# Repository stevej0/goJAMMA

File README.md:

# goJAMMA
Game on JAMMA development board PROTOTYPE v0.2 (C) 2019 Steve Jones / BONEYARD

This is a prototype FPGA based JAMMA board for the development of homebrew games for arcade machine platforms and superguns.

The design is currently in a prototype stage, pretty much everything has been tested as working, however bugs and performance issues may remain. This design is NOT approved for production as of yet, but the files are made public as an aid to others developing their own hardware.
  
FAQ to follow...

Hardware specifications (fixed):

Altera MAX10 10M25SAE FPGA, 25K logic elements, extended Flash features  
1MB 8Bit Static RAM, 10ns access  
16MB 8Bit HyperRAM, 166Mhz DDR, 128 byte burst  
48Mhz Crystal clock oscillator  
microSD card interface  
ADC 4 channel, 10 bit analog to digital convertor (Analog inputs via expansion connector)  
Buffered video output  
Stereo audio amplifier, 11 Watts  
PCM5101 Stereo 12S DAC  
4 Way Dip Switch  
Standard JAMMA 5v tolerant inputs, plus configuration jumpers for 6-button Pandoras Box style interface  
1x USER button, 1x RESET button  
1x USER LED  
Large long-life and user replacable through hole capacitors in the audio and voltage regulator sections  

Homebrew logic core (basic wishlist) specifications, likely to change:
  
CPU core (undecided, but a 6502 at 4Mhz currently works well)  
256 Colour palette, 320 x 240 pixel framebuffer (double buffered)  
Sprites (undecided, most likely a blitter for the framebuffer with fast HyperRAM as gfx data source)  
Layers (undecided, at least one text overlay, maybe a tiled background layer also)  
16 channel sample playback  
Ability to load programs and data from microSD fat32 formatted cards

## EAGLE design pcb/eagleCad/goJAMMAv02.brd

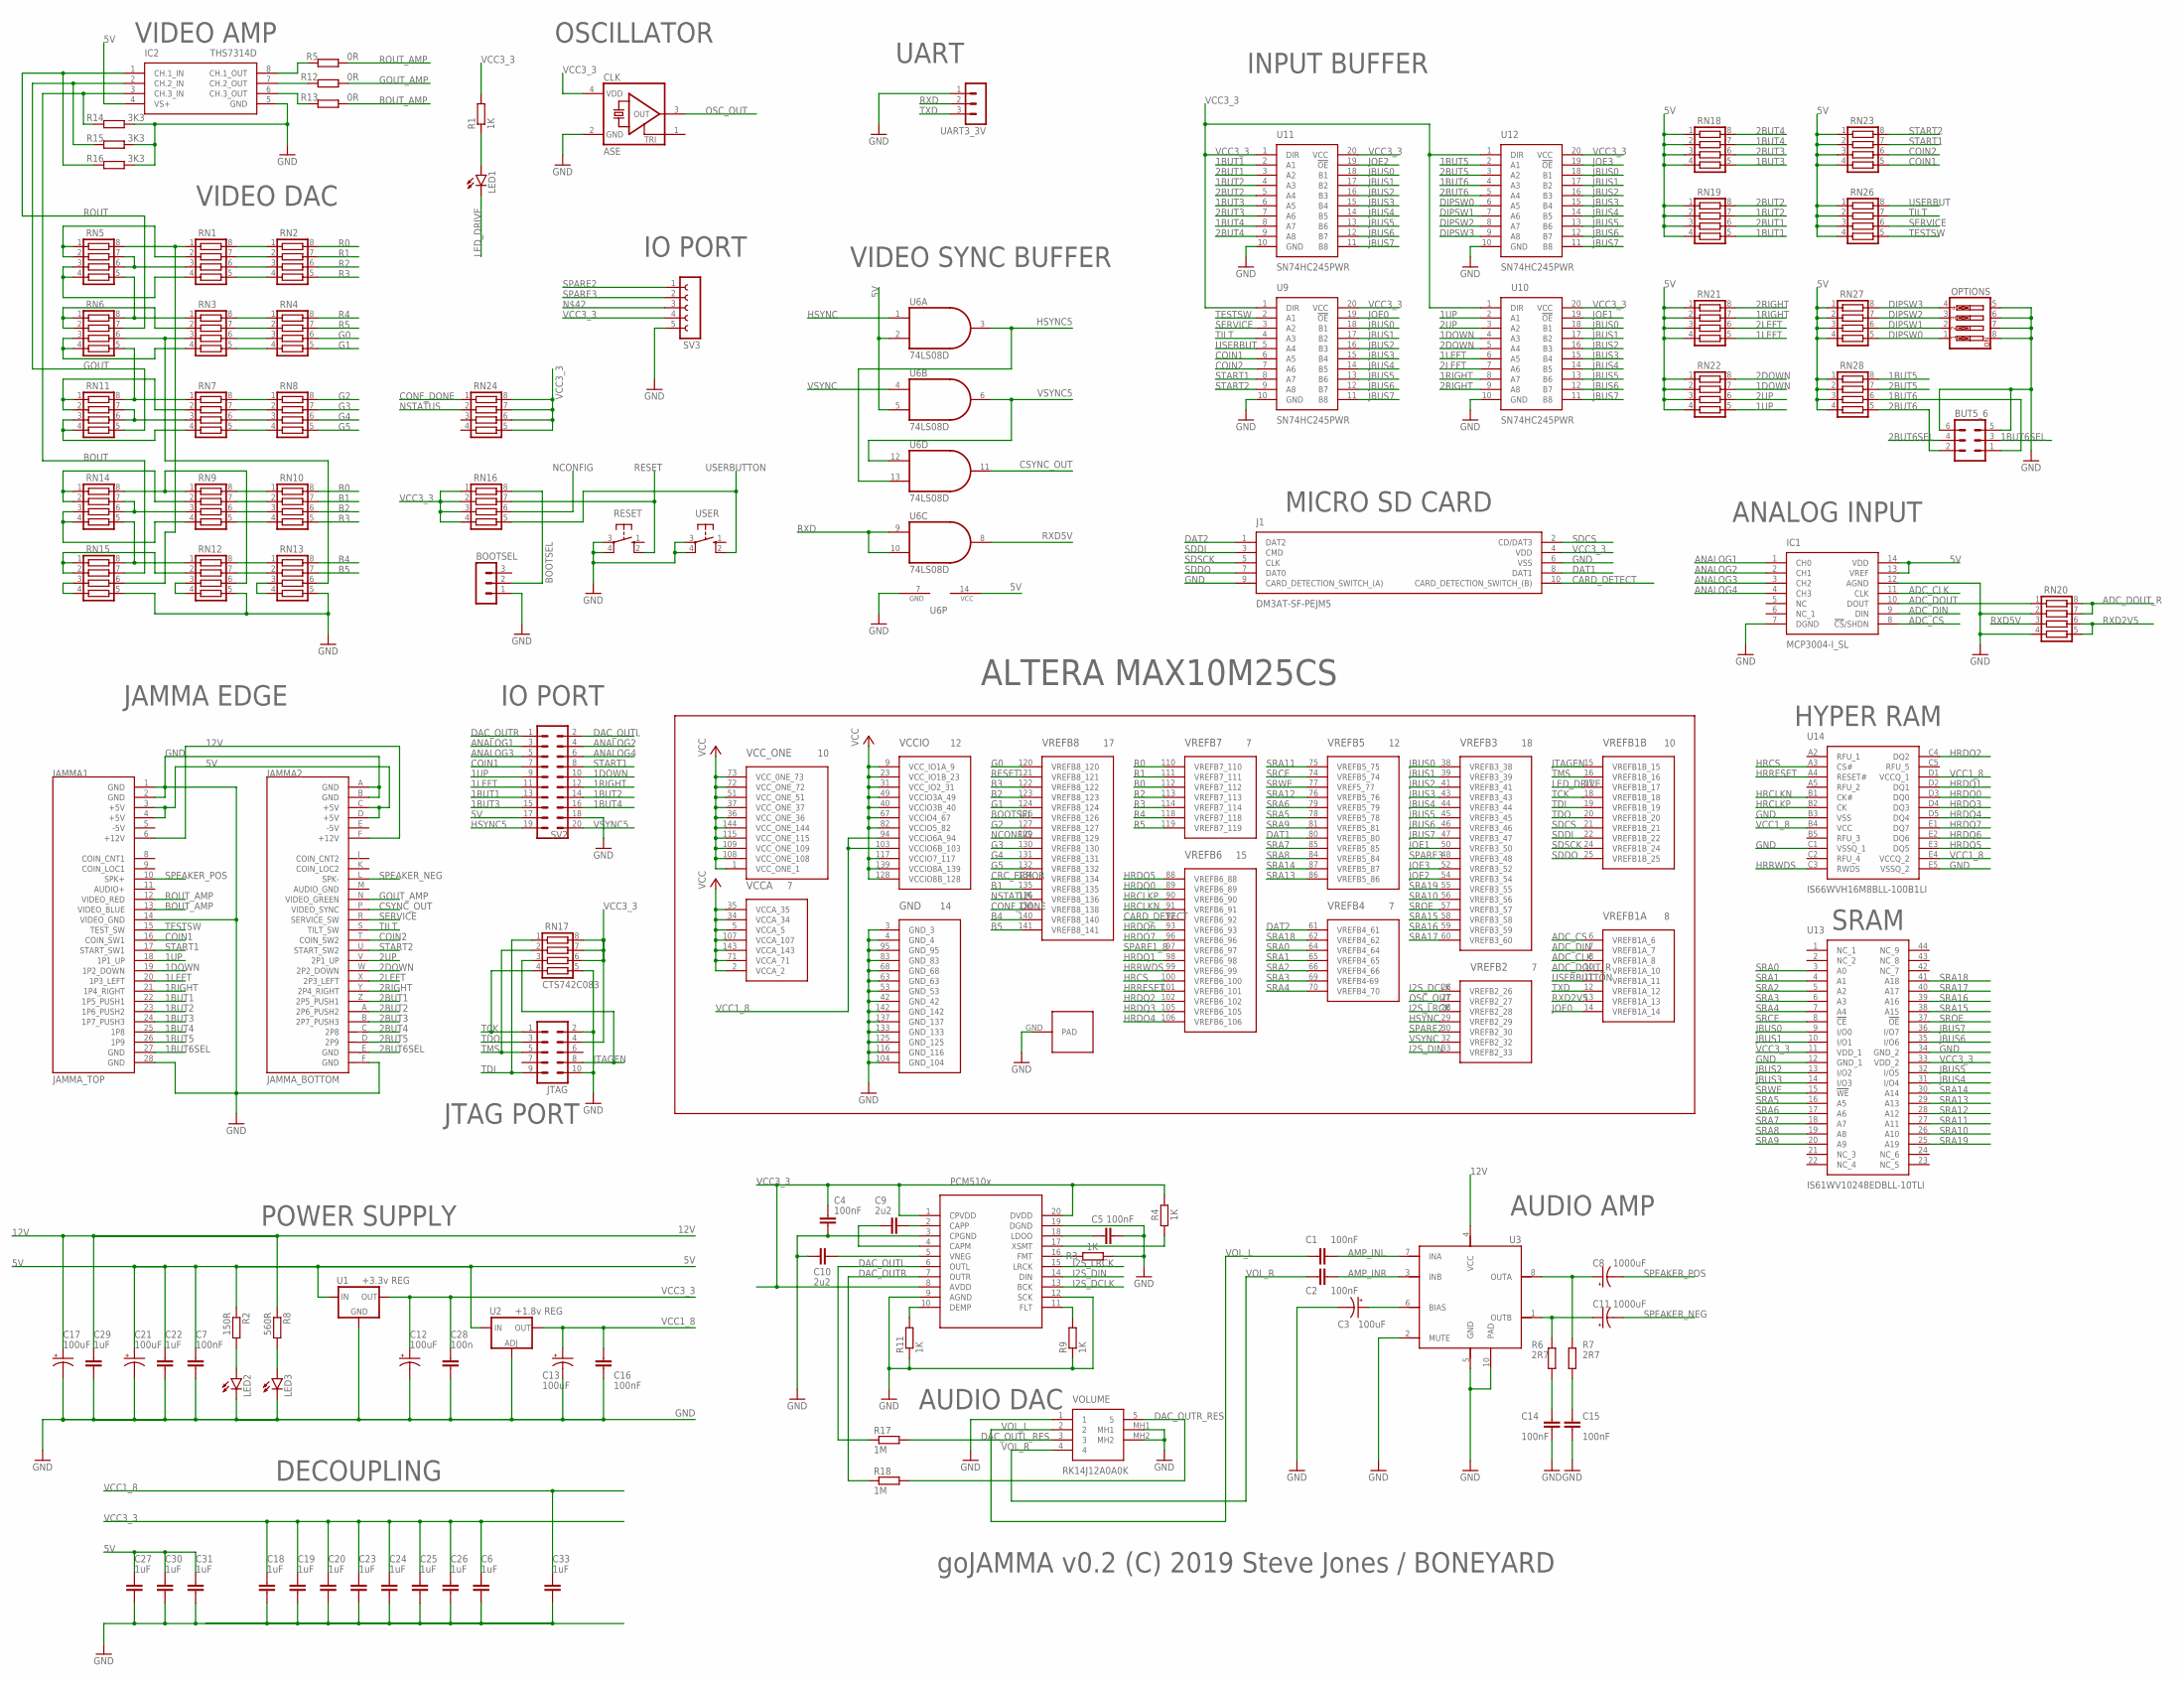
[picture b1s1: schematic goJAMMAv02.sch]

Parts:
BOOTSEL: MA03-1
BUT5_6: MA03-2
C1, C2, C4, C5, C7, C14, C15, C16: 100nF; C0805K
C3: 100uF; CPOL-RADIAL-2.5MM-6.5MM
C6, C18, C19, C20, C22, C23, C24, C25, C26, C27, C29, C30, C31, C33: 1uF; C0805K
C8, C11: 1000uF; CPOL-RADIAL-5MM-10MM
C9, C10: 2u2; C0805K
C12, C13, C17, C21: 100uF; CPOL-RADIAL-5MM-10MM
C28: 100n; C0805K
CLK: ASE
IC1: MCP3004-I_SL; SOIC127P600X175-14N
IC2: THS7314D; SOIC127P600X175-8N
J1: DM3AT-SF-PEJM5; DM3AT-SF-PEJM5_1
JAMMA1: JAMMA_TOP
JAMMA2: JAMMA_BOTTOM
JTAG: MA05-2
LED1, LED2, LED3: LEDCHIPLED_0805; CHIPLED_0805
OPTIONS: SW_DIP-4; EDG-04
R1, R3, R4, R9, R11: 1K; R0805
R2: 150R; R0805
R5, R12, R13: 0R; R0805
R6, R7: 2R7; R0805
R8: 560R; R0805
R14, R15, R16: 3K3; R0805
R17, R18: 1M; R0805
RESET: 10-XX; B3F-10XX
RN1, RN2, RN3, RN4, RN5, RN6, RN7, RN8, RN9, RN10, RN11, RN12, RN13, RN14, RN15, RN16, RN17, RN18, RN19, RN20, RN21, RN22, RN23, RN24, RN26, RN27, RN28: CTS742C083
SV2: MA10-2
SV3: FE05-1
U1: +3.3v REG; TO-252
U2: +1.8v REG; SOT223
U3: LM4755; DDPAK-9
U4: PCM5101; TSSOP20
U6: 74LS08D; SO14
U8: ALTERA_MAX10M25SCPAD; ALTERA_EQFP144
U9, U10, U11, U12: SN74HC245PWR; SOP65P640X120-20N
U13: IS61WV10248EDBLL-10TLI; SOP80P1176X120-44N
U14: IS66WVH16M8BLL-100B1LI; BGA24C100P5X5_600X800X120
UART3_3V: MA03-1
USER: 10-XX; B3F-10XX
VOLUME: RK14J12A0A0K

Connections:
1BUT1: JAMMA1.22 (1P5_PUSH1), RN19.5, SV2.13, U11.2 (A1)
1BUT2: JAMMA1.23 (1P6_PUSH2), RN19.7, SV2.14, U11.4 (A3)
1BUT3: JAMMA1.24 (1P7_PUSH3), RN18.5, SV2.15, U11.6 (A5)
1BUT4: JAMMA1.25 (1P8), RN18.7, SV2.16, U11.8 (A7)
1BUT5: JAMMA1.26 (1P9), RN28.8, U12.2 (A1)
1BUT6: BUT5_6.1, RN28.6, U12.4 (A3)
1BUT6SEL: BUT5_6.3, JAMMA1.27 (GND)
1DOWN: JAMMA1.19 (1P2_DOWN), RN22.7, SV2.10, U10.4 (A3)
1LEFT: JAMMA1.20 (1P3_LEFT), RN21.5, SV2.11, U10.6 (A5)
1RIGHT: JAMMA1.21 (1P4_RIGHT), RN21.7, SV2.12, U10.8 (A7)
1UP: JAMMA1.18 (1P1_UP), RN22.5, SV2.9, U10.2 (A1)
2BUT1: JAMMA2.Z (2P5_PUSH1), RN19.6, U11.3 (A2)
2BUT2: JAMMA2._A (2P6_PUSH2), RN19.8, U11.5 (A4)
2BUT3: JAMMA2._B (2P7_PUSH3), RN18.6, U11.7 (A6)
2BUT4: JAMMA2._C (2P8), RN18.8, U11.9 (A8)
2BUT5: JAMMA2._D (2P9), RN28.7, U12.3 (A2)
2BUT6: BUT5_6.2, RN28.5, U12.5 (A4)
2BUT6SEL: BUT5_6.4, JAMMA2._E (GND)
2DOWN: JAMMA2.W (2P2_DOWN), RN22.8, U10.5 (A4)
2LEFT: JAMMA2.X (2P3_LEFT), RN21.6, U10.7 (A6)
2RIGHT: JAMMA2.Y (2P4_RIGHT), RN21.8, U10.9 (A8)
2UP: JAMMA2.V (2P1_UP), RN22.6, U10.3 (A2)
5V: C7.1, C21.+, C22.1, C27.1, C30.1, C31.1, IC1.13 (VREF), IC1.14 (VDD), IC2.4 (VS+), JAMMA1.3 (+5V), JAMMA1.4 (+5V), JAMMA2.C (+5V), JAMMA2.D (+5V), R2.1, RN18.1, RN18.2, RN18.3, RN18.4, RN19.1, RN19.2, RN19.3, RN19.4, RN21.1, RN21.2, RN21.3, RN21.4, RN22.1, RN22.2, RN22.3, RN22.4, RN23.1, RN23.2, RN23.3, RN23.4, RN26.1, RN26.2, RN26.3, RN26.4, RN27.1, RN27.2, RN27.3, RN27.4, RN28.1, RN28.2, RN28.3, RN28.4, SV2.17, U1.1 (IN), U2.3 (IN), U6.2 (I1), U6.5 (I1), U6.14 (VCC)
12V: C17.+, C29.1, JAMMA1.6 (+12V), JAMMA2.F (+12V), R8.1, U3.4 (VCC)
-5V: JAMMA1.5 (-5V), JAMMA2.E (-5V)
ADC_CLK: IC1.11 (CLK), U8.8 (VREFB1A_8)
ADC_CS: IC1.8 (!CS!/SHDN), U8.6 (VREFB1A_6)
ADC_DIN: IC1.9 (DIN), U8.7 (VREFB1A_7)
ADC_DOUT: IC1.10 (DOUT), RN20.1
ADC_DOUT_R: RN20.7, RN20.8, U8.10 (VREFB1A_10)
AMP_INL: C1.2, U3.7 (INA)
AMP_INR: C2.2, U3.3 (INB)
ANALOG1: IC1.1 (CH0), SV2.3
ANALOG2: IC1.2 (CH1), SV2.4
ANALOG3: IC1.3 (CH2), SV2.5
ANALOG4: IC1.4 (CH3), SV2.6
B0: RN10.8, U8.112 (VREFB7_112)
B1: RN10.7, U8.135 (VREFB8_135)
B2: RN10.6, U8.123 (VREFB8_123)
B3: RN10.5, U8.122 (VREFB8_122)
B4: RN13.8, U8.140 (VREFB8_140)
B5: RN13.7, U8.141 (VREFB8_141)
BOOTSEL: BOOTSEL.2, RN16.8, U8.126 (VREFB8_126)
BOUT: IC2.3 (CH.3_IN), R14.2, RN15.7
BOUT_AMP: JAMMA1.13 (VIDEO_BLUE), R13.2
CARD_DETECT: J1.10 (CARD_DETECTION_SWITCH_(B)), U8.92 (VREFB6_92)
COIN1: JAMMA1.16 (COIN_SW1), RN23.5, SV2.7, U9.6 (A5)
COIN2: JAMMA2.T (COIN_SW2), RN23.6, U9.7 (A6)
CONF_DONE: RN24.1, U8.138 (VREFB8_138)
CRC_ERROR: U8.134 (VREFB8_134)
CSYNC_OUT: JAMMA2.P (VIDEO_SYNC), U6.11 (O)
DAC_OUTL: R17.1, SV2.2, U4.6 (OUTL)
DAC_OUTL_RES: R17.2, VOLUME.3
DAC_OUTR: R18.1, SV2.1, U4.7 (OUTR)
DAC_OUTR_RES: R18.2, VOLUME.5
DAT1: J1.8 (DAT1), U8.80 (VREFB5_80)
DAT2: J1.1 (DAT2), U8.61 (VREFB4_61)
DIPSW0: OPTIONS.1, RN27.5, U12.6 (A5)
DIPSW1: OPTIONS.2, RN27.6, U12.7 (A6)
DIPSW2: OPTIONS.3, RN27.7, U12.8 (A7)
DIPSW3: OPTIONS.4, RN27.8, U12.9 (A8)
G0: RN4.6, U8.120 (VREFB8_120)
G1: RN4.5, U8.124 (VREFB8_124)
G2: RN8.8, U8.127 (VREFB8_127)
G3: RN8.7, U8.130 (VREFB8_130)
G4: RN8.6, U8.131 (VREFB8_131)
G5: RN8.5, U8.132 (VREFB8_132)
GND: BOOTSEL.1, BUT5_6.5, BUT5_6.6, C3.2 (-), C4.2, C5.2, C6.2, C7.2, C10.2, C12.-, C13.-, C14.2, C15.2, C16.2, C17.-, C18.2, C19.2, C20.2, C21.-, C22.2, C23.2, C24.2, C25.2, C26.2, C27.2, C28.2, C29.2, C30.2, C31.2, C33.2, CLK.2 (GND), IC1.7 (DGND), IC1.12 (AGND), IC2.5 (GND), J1.6 (VSS), J1.9 (CARD_DETECTION_SWITCH_(A)), JAMMA1.1 (GND), JAMMA1.2 (GND), JAMMA1.14 (VIDEO_GND), JAMMA1.28 (GND), JAMMA2.A (GND), JAMMA2.B (GND), JAMMA2._F (GND), JTAG.2, JTAG.10, LED2.C, LED3.C, OPTIONS.5, OPTIONS.6, OPTIONS.7, OPTIONS.8, R3.1, R9.1, R11.1, R14.1, R15.1, R16.1, RESET.3, RESET.4 (P1), RN12.5, RN13.5, RN15.5, RN17.5, RN20.2, RN20.4, SV2.18, SV3.5, U1.3 (GND), U2.1 (ADJ), U3.2 (MUTE), U3.5 (GND), U3.10 (PAD), U4.3 (CPGND), U4.9 (AGND), U4.12 (SCK), U4.19 (DGND), U6.7 (GND), U8.3 (GND_3), U8.4 (GND_4), U8.42 (GND_42), U8.53 (GND_53), U8.63 (GND_63), U8.68 (GND_68), U8.83 (GND_83), U8.95 (GND_95), U8.104 (GND_104), U8.116 (GND_116), U8.125 (GND_125), U8.133 (GND_133), U8.137 (GND_137), U8.142 (GND_142), U8.GND (PAD), U9.10 (GND), U10.10 (GND), U11.10 (GND), U12.10 (GND), U13.12 (GND_1), U13.34 (GND_2), U14.B3 (VSS), U14.C1 (VSSQ_1), U14.E5 (VSSQ_2), UART3_3V.1, USER.3, USER.4 (P1), VOLUME.1, VOLUME.MH1, VOLUME.MH2
GOUT: IC2.2 (CH.2_IN), R15.2, RN11.5
GOUT_AMP: JAMMA2.N (VIDEO_GREEN), R12.2
HRCLKN: U8.91 (VREFB6_91), U14.B1 (CK#)
HRCLKP: U8.90 (VREFB6_90), U14.B2 (CK)
HRCS: U8.100 (VREFB6_100), U14.A3 (CS#)
HRDQ0: U8.89 (VREFB6_89), U14.D3 (DQ0)
HRDQ1: U8.98 (VREFB6_98), U14.D2 (DQ1)
HRDQ2: U8.102 (VREFB6_102), U14.C4 (DQ2)
HRDQ3: U8.105 (VREFB6_105), U14.D4 (DQ3)
HRDQ4: U8.106 (VREFB6_106), U14.D5 (DQ4)
HRDQ5: U8.88 (VREFB6_88), U14.E3 (DQ5)
HRDQ6: U8.93 (VREFB6_93), U14.E2 (DQ6)
HRDQ7: U8.96 (VREFB6_96), U14.E1 (DQ7)
HRRESET: U8.101 (VREFB6_101), U14.A4 (RESET#)
HRRWDS: U8.99 (VREFB6_99), U14.C3 (RWDS)
HSYNC: U6.1 (I0), U8.29 (VREFB2_29)
HSYNC5: SV2.19, U6.3 (O), U6.13 (I1)
I2S_DCLK: U4.13 (BCK), U8.26 (VREFB2_26)
I2S_DIN: U4.14 (DIN), U8.33 (VREFB2_33)
I2S_LRCK: U4.15 (LRCK), U8.28 (VREFB2_28)
JBUS0: U8.38 (VREFB3_38), U9.18 (B1), U10.18 (B1), U11.18 (B1), U12.18 (B1), U13.9 (I/O0)
JBUS1: U8.39 (VREFB3_39), U9.17 (B2), U10.17 (B2), U11.17 (B2), U12.17 (B2), U13.10 (I/O1)
JBUS2: U8.41 (VREFB3_41), U9.16 (B3), U10.16 (B3), U11.16 (B3), U12.16 (B3), U13.13 (I/O2)
JBUS3: U8.43 (VREFB3_43), U9.15 (B4), U10.15 (B4), U11.15 (B4), U12.15 (B4), U13.14 (I/O3)
JBUS4: U8.44 (VREFB3_44), U9.14 (B5), U10.14 (B5), U11.14 (B5), U12.14 (B5), U13.31 (I/O4)
JBUS5: U8.45 (VREFB3_45), U9.13 (B6), U10.13 (B6), U11.13 (B6), U12.13 (B6), U13.32 (I/O5)
JBUS6: U8.46 (VREFB3_46), U9.12 (B7), U10.12 (B7), U11.12 (B7), U12.12 (B7), U13.35 (I/O6)
JBUS7: U8.47 (VREFB3_47), U9.11 (B8), U10.11 (B8), U11.11 (B8), U12.11 (B8), U13.36 (I/O7)
JOE0: U8.14 (VREFB1A_14), U9.19 (!OE)
JOE1: U8.50 (VREFB3_50), U10.19 (!OE)
JOE2: U8.54 (VREFB3_54), U11.19 (!OE)
JOE3: U8.52 (VREFB3_52), U12.19 (!OE)
JTAGEN: JTAG.8, RN17.3, U8.15 (VREFB1B_15)
LED_DRIVE: LED1.C, U8.17 (VREFB1B_17)
unnamed: RN1.8, RN2.1
unnamed: C8.+, R7.2, U3.8 (OUTA)
unnamed: RN1.7, RN2.2
unnamed: RN1.6, RN2.3
unnamed: RN1.5, RN2.4
unnamed: RN3.8, RN4.1
unnamed: RN3.7, RN4.2
unnamed: RN7.8, RN8.1
unnamed: RN7.7, RN8.2
unnamed: RN7.6, RN8.3
unnamed: RN7.5, RN8.4
unnamed: RN6.5, RN7.1, RN11.8
unnamed: RN9.8, RN10.1
unnamed: RN1.1, RN5.8, RN15.6
unnamed: RN1.2, RN5.1, RN5.2
unnamed: RN1.3, RN5.6, RN5.7
unnamed: RN1.4, RN5.3, RN5.4
unnamed: RN3.1, RN5.5, RN6.8
unnamed: RN3.2, RN6.1, RN6.2
unnamed: RN9.7, RN10.2
unnamed: RN7.2, RN11.1, RN11.2
unnamed: RN7.3, RN11.6, RN11.7
unnamed: RN7.4, RN11.3, RN11.4
unnamed: RN9.6, RN10.3
unnamed: RN9.5, RN10.4
unnamed: RN3.4, RN6.3, RN6.4
unnamed: RN12.8, RN13.1
unnamed: RN3.6, RN4.3
unnamed: RN3.5, RN4.4
unnamed: RN3.3, RN6.6, RN13.6
unnamed: RN12.7, RN13.2
unnamed: RN9.1, RN12.6, RN14.8
unnamed: RN9.2, RN14.1, RN14.2
unnamed: RN9.3, RN14.6, RN14.7
unnamed: RN9.4, RN14.3, RN14.4
unnamed: RN12.1, RN14.5, RN15.8
unnamed: RN12.2, RN15.1, RN15.2
unnamed: RN15.3, RN15.4
unnamed: RN12.3, RN12.4
unnamed: RN13.3, RN13.4
unnamed: R3.2, U4.16 (FMT)
unnamed: IC2.8 (CH.1_OUT), R5.1
unnamed: LED1.A, R1.1
unnamed: IC2.7 (CH.2_OUT), R12.1
unnamed: IC2.6 (CH.3_OUT), R13.1
unnamed: LED2.A, R2.2
unnamed: LED3.A, R8.2
unnamed: C9.2, U4.2 (CAPP)
unnamed: C9.1, U4.4 (CAPM)
unnamed: C11.+, R6.2, U3.1 (OUTB)
unnamed: C3.1 (+), U3.6 (BIAS)
unnamed: C14.1, R6.1
unnamed: C15.1, R7.1
unnamed: C10.1, U4.5 (VNEG)
unnamed: R4.1, U4.17 (XSMT)
unnamed: R11.2, U4.10 (DEMP)
unnamed: R9.2, U4.11 (FLT)
unnamed: C5.1, U4.18 (LDOO)
NCONFIG: RN16.6, U8.129 (VREFB8_129)
NSTATUS: RN24.2, U8.136 (VREFB8_136)
OSC_OUT: CLK.3 (OUT), U8.27 (VREFB2_27)
R0: RN2.8, U8.110 (VREFB7_110)
R1: RN2.7, U8.111 (VREFB7_111)
R2: RN2.6, U8.113 (VREFB7_113)
R3: RN2.5, U8.114 (VREFB7_114)
R4: RN4.8, U8.118 (VREFB7_118)
R5: RN4.7, U8.119 (VREFB7_119)
RESET: RESET.2 (S1), RN16.7, U8.121 (VREFB8_121)
ROUT: IC2.1 (CH.1_IN), R16.2, RN6.7
ROUT_AMP: JAMMA1.12 (VIDEO_RED), R5.2
RXD: U6.9 (I0), U6.10 (I1), UART3_3V.2
RXD2V5: RN20.5, RN20.6, U8.13 (VREFB1A_13)
RXD5V: RN20.3, U6.8 (O)
SDCS: J1.2 (CD/DAT3), U8.21 (VREFB1B_21)
SDDI: J1.3 (CMD), U8.22 (VREFB1B_22)
SDDO: J1.7 (DAT0), U8.25 (VREFB1B_25)
SDSCK: J1.5 (CLK), U8.24 (VREFB1B_24)
SERVICE: JAMMA2.R (SERVICE_SW), RN26.6, U9.3 (A2)
SPARE1_8: U8.97 (VREFB6_97)
SPARE2: SV3.1, U8.30 (VREFB2_30)
SPARE3: SV3.2, U8.48 (VREFB3_48)
SPEAKER_NEG: C11.-, JAMMA2.L (SPK-)
SPEAKER_POS: C8.-, JAMMA1.10 (SPK+)
SRA0: U8.64 (VREFB4_64), U13.3 (A0)
SRA1: U8.65 (VREFB4_65), U13.4 (A1)
SRA2: U8.66 (VREFB4_66), U13.5 (A2)
SRA3: U8.69 (VREFB4-69), U13.6 (A3)
SRA4: U8.70 (VREFB4_70), U13.7 (A4)
SRA5: U8.78 (VREFB5_78), U13.16 (A5)
SRA6: U8.79 (VREFB5_79), U13.17 (A6)
SRA7: U8.85 (VREFB5_85), U13.18 (A7)
SRA8: U8.84 (VREFB5_84), U13.19 (A8)
SRA9: U8.81 (VREFB5_81), U13.20 (A9)
SRA10: U8.56 (VREFB3_56), U13.26 (A10)
SRA11: U8.75 (VREFB5_75), U13.27 (A11)
SRA12: U8.76 (VREFB5_76), U13.28 (A12)
SRA13: U8.86 (VREFB5_86), U13.29 (A13)
SRA14: U8.87 (VREFB5_87), U13.30 (A14)
SRA15: U8.58 (VREFB3_58), U13.38 (A15)
SRA16: U8.59 (VREFB3_59), U13.39 (A16)
SRA17: U8.60 (VREFB3_60), U13.40 (A17)
SRA18: U8.62 (VREFB4_62), U13.41 (A18)
SRA19: U8.55 (VREFB3_55), U13.25 (A19)
SRCE: U8.74 (VREFB5_74), U13.8 (!CE)
SROE: U8.57 (VREFB3_57), U13.37 (!OE)
SRWE: U8.77 (VREF5_77), U13.15 (!WE)
START1: JAMMA1.17 (START_SW1), RN23.7, SV2.8, U9.8 (A7)
START2: JAMMA2.U (START_SW2), RN23.8, U9.9 (A8)
TCK: JTAG.1, RN17.4, U8.18 (VREFB1B_18)
TDI: JTAG.9, RN17.1, U8.19 (VREFB1B_19)
TDO: JTAG.3, U8.20 (VREFB1B_20)
TESTSW: JAMMA1.15 (TEST_SW), RN26.5, U9.2 (A1)
TILT: JAMMA2.S (TILT_SW), RN26.7, U9.4 (A3)
TMS: JTAG.5, RN17.2, U8.16 (VREFB1B_16)
TXD: U8.12 (VREFB1A_12), UART3_3V.3
USERBUT: RN26.8, U9.5 (A4)
USERBUTTON: RN16.5, U8.11 (VREFB1A_11), USER.2 (S1)
VCC1_8: C13.+, C16.1, C33.1, U2.2 (OUT), U2.4 (OUT), U8.94 (VCCIO6A_94), U8.103 (VCCIO6B_103), U14.B4 (VCC), U14.D1 (VCCQ_1), U14.E4 (VCCQ_2)
VCC3_3: C4.1, C6.1, C12.+, C18.1, C19.1, C20.1, C23.1, C24.1, C25.1, C26.1, C28.1, CLK.4 (VDD), J1.4 (VDD), JTAG.4, R1.2, R4.2, RN16.1, RN16.2, RN16.3, RN16.4, RN17.6, RN17.7, RN17.8, RN24.5, RN24.6, RN24.7, RN24.8, SV3.4, U1.2 (OUT), U4.1 (CPVDD), U4.8 (AVDD), U4.20 (DVDD), U8.1 (VCC_ONE_1), U8.2 (VCCA_2), U8.5 (VCCA_5), U8.9 (VCC_IO1A_9), U8.23 (VCC_IO1B_23), U8.31 (VCC_IO2_31), U8.34 (VCCA_34), U8.35 (VCCA_35), U8.36 (VCC_ONE_36), U8.37 (VCC_ONE_37), U8.40 (VCCIO3B_40), U8.49 (VCCIO3A_49), U8.51 (VCC_ONE_51), U8.67 (VCCIO4_67), U8.71 (VCCA_71), U8.72 (VCC_ONE_72), U8.73 (VCC_0NE_73), U8.82 (VCCIO5_82), U8.107 (VCCA_107), U8.108 (VCC_ONE_108), U8.109 (VCC_ONE_109), U8.115 (VCC_ONE_115), U8.117 (VCCIO7_117), U8.128 (VCCIO8B_128), U8.139 (VCCIO8A_139), U8.143 (VCCA_143), U8.144 (VCC_ONE_144), U9.1 (DIR), U9.20 (VCC), U10.1 (DIR), U10.20 (VCC), U11.1 (DIR), U11.20 (VCC), U12.1 (DIR), U12.20 (VCC), U13.11 (VDD_1), U13.33 (VDD_2)
VOL_L: C1.1, VOLUME.2
VOL_R: C2.1, VOLUME.4
VSYNC: U6.4 (I0), U8.32 (VREFB2_32)
VSYNC5: SV2.20, U6.6 (O), U6.12 (I0)

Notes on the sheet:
IO PORT
JAMMA EDGE
JTAG PORT
AUDIO DAC
AUDIO AMP
ANALOG INPUT
HYPER RAM
SRAM
UART
MICRO SD CARD
INPUT BUFFER
VIDEO AMP
VIDEO DAC
POWER SUPPLY
DECOUPLING
VIDEO SYNC BUFFER
OSCILLATOR
goJAMMA v0.2 (C) 2019 Steve Jones / BONEYARD

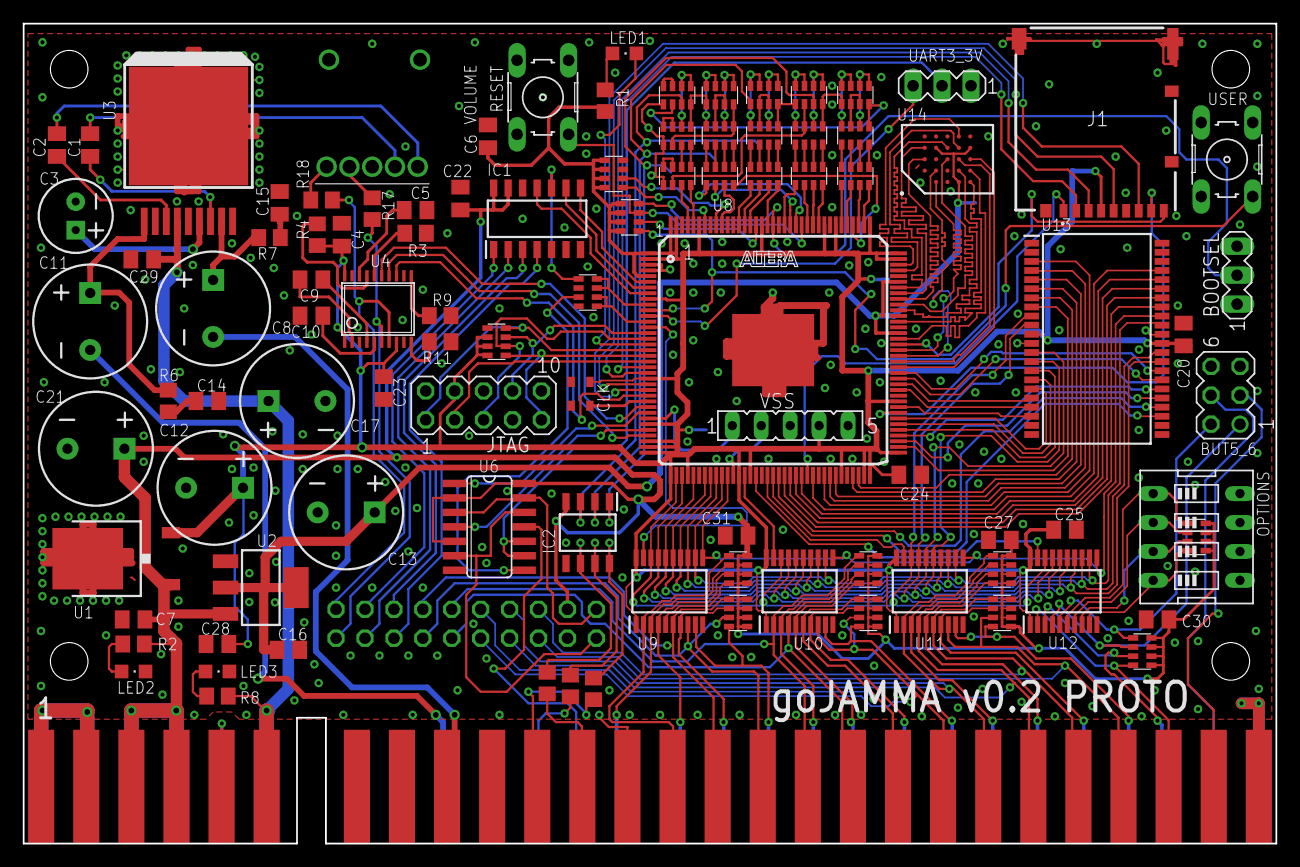
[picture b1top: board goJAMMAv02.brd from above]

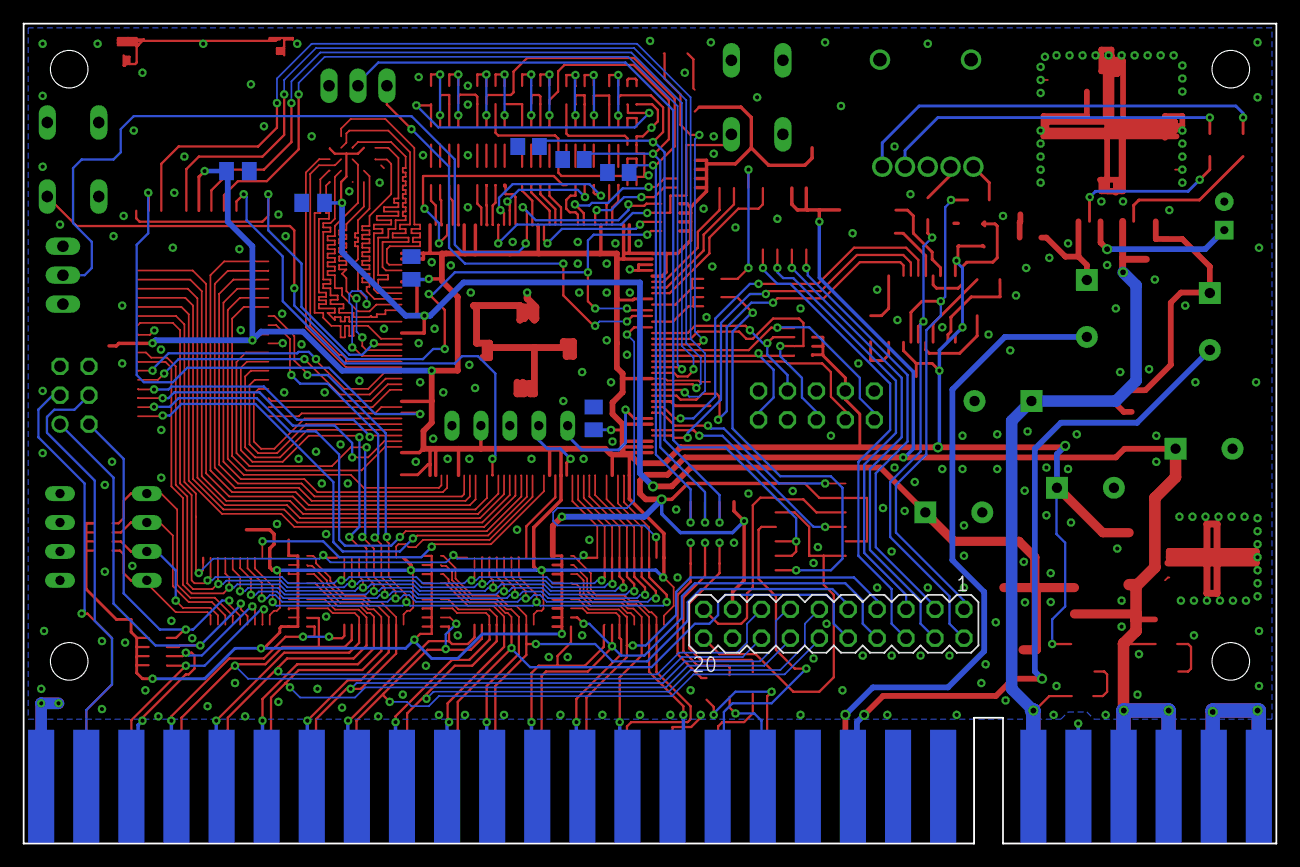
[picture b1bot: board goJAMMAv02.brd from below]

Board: 2 copper layers, 110.0 x 72.0 mm, 111 parts (8 on the bottom side), 223 nets.

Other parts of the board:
E$1, E$2, E$8, E$9: STAND-OFF

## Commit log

2019-05-22 Create derp
2019-05-23 Update LICENSE
2019-05-24 Create ignore

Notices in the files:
parts and their libraries:
SparkFun-Capacitors: Licensing: Creative Commons ShareAlike 4.0 International - https://creativecommons.org/licenses/by-sa/4.0
